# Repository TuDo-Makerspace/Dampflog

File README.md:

# Dampflog <!-- omit in toc -->

A synthesizer built from an [old Conrad Train whistle PCB](docs/DLP_Manual.pdf)

> This project was created during the [TU-DO Makerspace's Makerthon #1](https://www.instagram.com/p/CwGRmoHKHiY/?igshid=MzRlODBiNWFlZA==)!

# Table Of Contents <!-- omit in toc -->
- ["Dampflockpfeife" - The Steam Locomotive Whistle](#dampflockpfeife---the-steam-locomotive-whistle)
	- [Product Description](#product-description)
	- [The Circuit](#the-circuit)
		- [1. Power stage](#1-power-stage)
		- [2. Trigger/Gate circuit](#2-triggergate-circuit)
		- [3. Oscillator](#3-oscillator)
		- [4. Output Stage/Amplifier](#4-output-stageamplifier)
- [Background - The Makerthon](#background---the-makerthon)
- [Hacking the PCB](#hacking-the-pcb)
	- [Power Input](#power-input)
	- [Audio Output](#audio-output)
	- [Original Controls](#original-controls)
	- [HOLD Switch](#hold-switch)
	- [Gate Input](#gate-input)
	- [Pitch Control](#pitch-control)
		- [Initial Approach](#initial-approach)
		- [Time to get serious](#time-to-get-serious)
		- [Screw CV, we're going full MIDI](#screw-cv-were-going-full-midi)
		- [A PCB to rule them all](#a-pcb-to-rule-them-all)
- [The Result](#the-result)
- [Future plans](#future-plans)

## "Dampflockpfeife" - The Steam Locomotive Whistle

> Pardon the crude picture, I unfortunately didn't take any pictures of the PCB before I started hacking it.

### Product Description

The "Dampflockpfeife" is a [Printed Circuit Board that was published by Conrad Electronics in 1997 as a DIY soldering set for model train enthusiasts](docs/DLP_Manual.pdf). It attempts to mimic the sound of a steam locomotive whistle when activated. The circuit board is intended to be integrated into a model train track setup, where it can be activated in response to a passing train. To adjust the whistle sound, the PCB features two potentiometers — one for adjusting the pitch and another for setting the duration of the whistle blast. Activating the sound requires short-circuiting two contacts on the PCB, which can be achieved, for example, by employing a button or a sensor mechanism.

Here's a showcase of how the Whistle sounds:

https://github.com/TU-DO-Makerspace/Dampflog/assets/12089409/401a1205-c79d-425e-badc-b6d5c987373b

As you can hear, it does somewhat resemble a steam locomotive whistle, albeit rather poorly. That being said, a digital solution at the time would likely have been signficantly more expensive.

### The Circuit

Given its publication date, it should not come as a surprise that this circuit is devoid of any digital components. The whistle sound is synthesized entirely through analog means. Fortunately, the PCB's manual is, despite its age, [readily accessible online](docs/DLP_Manual.pdf). It offers a comprehensive resource, featuring a circuit description, a complete schematic, and even a PCB layout. While the manual is in German, fear not, as we will provide a comprehensive coverage of the circuit here.

Here's the schematic of the circuit:

The circuit can be split into four parts:

- 1. Power stage
- 2. Trigger/Gate circuit
- 3. Oscillator
- 4. Output Stage/Amplifier

#### 1. Power stage

On the first glance we can recognize a full bridge rectifier, indicating that the Circuit takes AC as an input. I initially found it somewhat peculiar but as I later found out, this choice was made to ensure compatibility with "Märklin" model train tracks, which, in contrast to their competitors, rely on AC voltage. According to various sources, this voltage typically falls within the range of 16 to 24 volts. While I'm no expert in model trains, I did have the fortunate opportunity to recently talk with someone knowledgeable in the field. They explained me that this unique reliance on AC voltage is a rather quirky characteristic of Märklin model trains.

Now, returning to the circuit itself: As mentioned, the AC voltage first passes through a full bridge rectifier (D1-D4) to convert it into a pulsating DC signal. Subsequently, this signal is smoothed out by a 100uF capacitor (C12). The stabilized voltage is then further regulated down to a consistent 12 volts via a 7812 linear regulator (IC1). This 12-volt output is then used as the supply voltage to power the remaining components of the circuit.

For my intents and purposes the whole power section was not needed. Instead, I simply used a 12V DC power supply and connected it directly to the 12V rail.

#### 2. Trigger/Gate circuit

As I delved into the schematic, one symbol immediately captured my attention: the NE555 timer IC. At first glance, I presumed it might be responsible for generating the whistle tone itself, but I quickly discovered that it operates in monostable/one-shot mode to generate a temporary gate signal. This gate signal serves to trigger the oscillator. Its duration is adjustable via potentiometer P2, allowing for a range spanning 1 to 10 seconds based on the potentiometer's setting.

To output a gate signal, a switch connected to the trigger input of the NE555 (labeled "Start" in the schematic) must be closed. This action pulls down the trigger pin and prompts the NE555 to produce a high signal at output pin 3, sustaining it for the preconfigured duration. This signal subsequently forward-biases transistor T3. Since the collector of T3 is connected to the base of T2, T2 becomes reverse-biased as a result. If no gate signal is present (default state), T2 is forward-biased via the pull-up resistor R4, which keeps the feedback path of the oscillator grounded, preventing it from generating any tone. With T2 in a reverse-biased state, the feedback path is no longer held down, enabling the oscillator to oscillate freely and synthesize the desired tone.

#### 3. Oscillator

The oscillator is arguably the most important part of the entire circuit. It somewhat resembles a relaxation oscillator built around an LM741 operational amplifier (OP-AMP), albeit with a distinct set of quirks that give it its unique character.

Firstly, the positive feedback loop takes an unusual turn as it's AC-coupled via capacitors C1 and C2. Further, what sets this oscillator apart and makes it particularly fascinating, is the inclusion of an NPN transistor, T1 within the feedback path. This transistor operates in a rather atypical diode configuration, with its emitter connected to the more positive rail. Its role? To introduce a subtle touch of chaos by injecting noise into the feedback path. But wait, there's more. The op-amp's output is also coupled to the "Offset Null" pin via capacitor C7, further contributing to the circuit's distinctive noisy sound. The noise injected into the feedback path causes subtle changes in the oscillator's frequency. This is precisely what gives this PCB its steam locomotive" sound. The rest of the circuit aligns more closely with a standard OP-AMP relaxation oscillator.

The frequency of this oscillator is adjustable through potentiometer P1, which defines the voltage propagated through the positive feedback pathway. On the inverting input of the OP-AMP, an RC circuit formed by R8 and C6 generates a triangular waveform. When P1's resistance decreases, the voltage in the positive feedback path decreases as well. Consequently, the triangular wave at the non-inverting input catches up to the inverting input faster, escalating the oscillator's frequency. When P1 reaches a low-enough resistance, the propagated voltage drops sufficiently low to stabilize the oscillation. In this state, only the eerie and somewhat spooky sound produced by the noise feedback path remains audible. You can listen to a recording of this peculiar sound [here](https://soundcloud.com/user-631734174/bc548-diode-configuration-noise).

An interesting side effect of this stabilization is that the oscillator experiences hysteriesys due to it's schmitt-trigger like positive feedback. As a result, P1 must be turned further back to retrigger the oscillation.

In total, the oscillator offers a frequency spectrum spanning approximately 116Hz (at infinite resistance) to 700Hz (at the point of stabilization). This equates to roughly 2.5 octaves of range, covering pitches from A#2 to F5.

Below are a couple of screenshots of LTSpice simulations to further illustrate the behaviour of the oscillator.

LT SPICE STUFF HERE

A crucial aspect of this circuit: The relationship between frequency and the potentiometer P1 follows an inversely multiplicative response. At lower resistances (corresponding to higher frequencies), even slight adjustments to P1 produce rapid frequency shifts. In contrast, at higher resistances (corresponding to lower frequencies), making similar changes to P1 yields only slight changes in frequency. Ideally, for precise pitch control, we would expect this behavior to be exponential, not inverse multiplicative. This characteristic became a significant challenge when attempting to implement 1V/Octave pitch control, as we will explore later.

Additionally, the LM741 exhibits an intersting trait: At higher frequencies, it exhibits a low-pass filtering effect. Lower frequencies result in a more square-like output, while higher frequencies manifest as a more triangular waveform. This phenomenon can likely be attributed to the slew rate of the LM741, and it controbutes to a distinctive and appealing character to the resulting sound.

#### 4. Output Stage/Amplifier

To be honest, I don't possess enough experience in the field of transistor amplifiers, and given that the output stage is not really relevant for my project, I haven't delved deeply into its functionality. I have a vague suspicion that T4 and T5 might play a role in amplifying the signal voltage, while the complementary push-pull amplifier comprising T7 and T6 might be responsible for current buffering. However, as mentioned, I'm not entirely certain so I welcome any corrections or clarifications if I'm off the mark.

## Background - The Makerthon

Before discussing the modifications I made to the circuit board, I'd like to provide some context for this project. This project was born out of a Hackathon organized at our Makerspace, called "Makerthon". The theme, albeit not mandatory, was to "Upcycle" old electronics that we had lying around in the Makerspace. The time frame for the Hackathon was about two and a half days.

During the first day the task was to scavange for old electronics and brainstorm ideas for potential projects. After digging through an old box of PCBs I stumbled upon the Dampflog PCB. From there, it didn't take long to find the manual online and jump to the idea of turning this thing into a musical synthesizer!

## Hacking the PCB

After thoroughly examining the circuit, it was time to transform the PCB into a musical synthesizer. Before I could wield my trusty soldering iron, I needed to formulate a roadmap of the features I wanted to "hack" into the PCB. Here's my initial list of requirements:

- 12V DC Power Input
- 3.5mm Jack audio output with volume control
- A HOLD switch to permanently enable the gate signal
- A 0-5V Gate input to trigger the gate signal
- A 1V/Octave CV input to control the pitch

Beyond these additions, I wanted to ensure that the device retained its original functionality. To achieve this, I included a push-button for manual gate signal triggering, along with potentiometers to adjust the gate signal duration and pitch manually.

For housing the PCB, I repurposed an old metal box that had once contained a [data transfer switch (KVM Switch)](https://www.amazon.com/Kentek-Parallel-Peripherals-Devices-Printer/dp/B07KWRWLRN)—which we happened to have lying around in the makerspace. Typically, I would have opted for a 3D-printed enclosure, but as mentioned prior, this project was created during a Hackathon, and I simply didn't have the luxury of time for enclosure design and printing. As a playful touch, I even gave the enclosure a neat little spray-paint job, just for the fun of it.

### Power Input

Adding a 12V DC power input was rather trivial. I simply connected a 2.1mm DC barrel jack to the 12V rail of the PCB with a switch in between to turn the device on and off. I also added a small red power LED next to the Jack to indicate that the device is powered on.

I tried to solder the power wires as close to the power stage as possible to maximize the utilization of the power capacitors on the PCB. The DC jack found its home on the front side of the enclosure, while the switch was thoughtfully situated on the back side.

In hindsight, I realize that it might have been more ergonomically advantageous to swap the positions of the jack and the switch.

PICTURE OF JACK HERE

### Audio Output

Adding audio output was also pretty straight forward. I simply connected a 3.5mm audio jack to the output of the amplifier. To provide volume control for the output signal, I introduced a potentiometer which serves as a voltage divider.

The potentiometer and jack were mounted on the front side of the enclosure for easy accessibility.

PICTURE OF AUDIO JACK HERE

It's important to know that the output can reach up to 10VPP, which is **NOT** suitable for headphones. I recommend only
using the device in combination with an audio interface or external amplifier. The volume should always be turned down first
before connecting the device to an audio interface or amplifier.

The advantage of such high peak-to-peak voltage is that it can be used to drive a speaker directly and can also interface easily with eurorack modules which also operate at similar voltage levels.

### Original Controls

As previously mentioned, it was essential to retain the device's original intended functionality. One addition was a green arcade-style push button mounted on the top side of the enclosure to serve as a trigger for the gate signal. I also mounted two potentiometers on the top side to control the duration of the gate signal and the pitch. It should be noted that I used a 200k pot instead the original inteded value of 50k. This modification expanded the available pitch range. A 50k pot couldn't quite reach the lower frequency limits of the oscillator.

PICTURE OF ORIGINAL CONTROLS HERE

### HOLD Switch

Incorporating a HOLD switch proved to be the first slightly more complicated addition to the circuit. After some consideration, I determined that a switch connected in parallel to transistor T3 would provide the most effective solution. When this switch is in the closed position, it essentially replicates the scenario where T3 is forward-biased. Consequently, this keeps T2 in a reverse-biased state, ensuring that the oscillator remains continually enabled.

For user convenience, the HOLD switch has been mounted next to the trigger button.

PICTURE OF HOLD SWITCH HERE

### Gate Input

To introduce a GATE support, I drew inspiration from the design of the HOLD switch. I incorporated a 3.5mm jack, connected to an NMOS transistor positioned in parallel with T3. To guarantee that the MOSFET remains consistently off when the jack is not used, I added a 220k Pull-Down resistor at the gate.

Additionally, for added protection against accidental voltage spikes (e.g., during jack cable insertion), I integrated a 10k resistor between the jack tip and the MOSFET's gate. This arrangement effectively increases the RC constant (C being the MOSFETS capacitance), safeguarding the MOSFET from potential damage.

PICTURE OF GATE JACK HERE

Without revealing too much ahead, I made some slight modifications to the GATE input during the course of the project. More on that later.

To put the GATE support to the test, I connected my trusyworthy Arturia Keystep to the GATE input, only to discover that the oscillator isn't particularly well-suited for GATE input, at least not in the traditional sense. You see, the oscillator exhibits a slight attack duration and a rather brief decay time. This means it requires a significant amount of time to reach its intended pitch but quickly ceases once the GATE signal drops. Consequently, rapid GATE signals fail to give the oscillator adequate time to achieve its intended pitch, resulting in a "chopped" tone. This behavior is primarily attributed to the fact that the oscillator relies on RC circuits, which are intentionally designed to take time to charge up.

Despite this, I still found the GATE input to be genuinely useful in only two scenarios:

- When the BPM/tempo setting allows the oscillator sufficient time to attain its desired pitch.
- When creating a percussive, choppy sound effect.

Interestingly, I found the second scenario to be a seriously cool unintended feature. It particularly shines when the oscillator is pushed to its upper limits, allowing only the noise within the feedback path to be gated. This makes for a dirty, industrial screechy sound which is great for harsher techno tracks. You can explore a sample of this distinctive sound, enhanced with a touch of distortion, reverb, flanging, and some percussion, by [clicking here](https://soundcloud.com/user-631734174/dampflog-gate-noise-test).

### Pitch Control

#### Initial Approach

To at least deliver a proof of concept for the end of the Makerthon I had to at least implement some form of half-arsed pitch control. For the sake of demonstration I
disattached the Pitch potentiometer P1 and soldered in a generic Jellybean transistor in place. Then I added a 3.5mm jack for a CV input and simply soldered it with a
voltage divider and rather large base resistor to the transistors base until I got a somewhat usable range of pitch. Obiously the scale was completely out of tune and far from linear, but It was enough to demonstrate that the thing can be used to produce melodies.

https://github.com/TU-DO-Makerspace/Dampflog/assets/12089409/d06b69a9-8a2e-4bfc-8f98-e92429bd2175

#### Time to get serious

Implementing pitch control became a weeks-long journey. By the end I had suffered from serious circuit design brain-rot. Prior to working on this project, my experience with analog operation of transistors was somewhat limited. This was further complicated by attempting to implement 1V/Oct pitch control on a circuit that was never originally designed for such a purpose. I also wanted to avoid altering the original circuit as much as possible.

After some initial, albeit clueless experimentation with transistors, it became very clear that I couldn't sidestep a deeper understanding of these components if I wanted to achieve precise 1V/Oct control. Fast forward a few weeks, and I had consumed over 40 hours of electronic circuits lectures delivered by Prof. Behzad Razavi from the University of California in Los Angeles, which are freely available online. I can't emphasize enough how invaluable these lectures were, providing a significantly more comprehensive and insightful overview of transistors compared to my university's electronic circuit course. After absorbing a substantial amount of knowledge from these lectures, I felt ready to take a more educated approach to solve the pitch control conundrum.

First, I examined how some Voltage-Controlled Oscillators (VCOs) implement 1V/Oct pitch control. Typically, this involves exponentializing a linear signal using a transistor. This exponentialization is necessary because human perception of pitch is inherently exponential. In the equal-tempered scale, for instance, the frequency of notes increases exponentially by the twelfth root of 2. Of course, the implementation goes beyond simply connecting a transistor's base to the 1V/Oct input; it typically includes circuitry for gain calibration, scaling, and base note adjustment. However, these details need not haunt us, as this approach cannot be directly applied to our oscillator anyaways.

Here's the crux of the issue: our oscillator exhibits inverse-multiplicative growth, something akin to the form a * 1/x + b. 

This response is neither linear nor exponential. If it were linear, we could simply use a transistor to exponentialize it and achieve 1V/Oct pitch control. If it were already exponential, we could use a transistor with heavily supressed gain, thus operating it nearly lineary (akin to a voltage-controlled resistor). Unfortunately, the oscillator's response falls into an awkward zone where it somewhat behaves like an exponential function but not quite. Yes, Low frequencies experience a slow rate of change, and high frequencies experience a rapid rate of change, but it's still not quite exponential. To test the extent of this inaccuracy, I decided to construct a test circuit with a transistor that roughly operated as a voltage-controlled resistor. To achieve this, I selected an extraordinarily large base resistor (around 5M in this case) to suppress the transistor's gain to the point where its beta value and base resistor dominated the gain.

The next step involved sweeping the transistor's base voltage using a function generator and measuring the oscillator's frequency. The outcome was predictably disappointing. As anticipated, the response exhibited inverse-multiplicative behavior, with the oscillator stabilizing at high frequencies. I unfortunately only measured the frequency response within the operating range of the
transistor, so to better illustrate the inverse-multiplicative behavior the graph below shows the frequency to base voltage response on a equivalent LTSpice simulated circuit:

It should be noted that the real oscillator does not reach frequencies below 116Hz, other than that the response is similar enough to demonstrate my point.

Notice the grey lines in the graph. These represent note intercepts. Taking a quick glance at the note intercepts, it becomes apparent that the response only approximates exponential pitch within an exceedingly narrow range. Ideally we'd want them to be equally spaced on the x axis to implement 1V/Oct. If we plot the distances between each note intercept, this discrepancy becomes even more pronounced. Here's actual data from the real oscillator:

As we can see pitch only behaves linearly proportional around 3.5V with a steps size of about 60mV/Note. For the setup in question, 3.5V corresponded to approximately 300Hz, which falls within the 4th octave. As we leave 3.5V this proportion begins to drift away from the close to constant 60mV, which will cause the pitch to become out of tune.

I actually went so far as to construct a 1V/Oct scaling circuit to connect my Keystep keyboard. While I achieved reasonably linear behavior in the fourth octave (as corresponding to the "sweet spot" where the inverse-multiplicative function is most similar to the exponential pitch function), venturing beyond the octave unsuprisingly resulted in severely out-of-tune frequencies. This deviation escalated significantly the further we moved away from this "sweet spot."

#### Screw CV, we're going full MIDI

At this point, it dawned on me that trying to tackle the inverse-multiplicative quirk with analog wizardry just wasn't worth the headache. I should probably mention that I'm currently pursuing a degree in computer engineering. Now, you know how it is – us computer engineers often enjoy poking fun at electrical engineers by solving problems with lines of code instead of soldering irons. Jokes aside, it really seemed like the easiest and most practical solution here was to go digital, and more specifically, to embrace the wonders of microcontrollers and DACs. And if we're making the switch to digital, why not go all the way and swap out CV with MIDI?

The idea is pretty straightforward: the MCU receives MIDI signals via a MIDI port, then converts them into DAC values using a handy lookup table. These DAC values, in turn, dictate the behavior of a transistor nestled within the oscillator's feedback path. Now, we no longer need to fuss about the intricacies of whether the oscillator operates linearly or exponentially. All we have to do is tell the MCU which note corresponds to which DAC value, and presto – we've got the right frequency.

With a DAC, it's still important to maintain control over the transistor's gain suppression while ensuring that the gain remains substantial enough to cover the oscillator's full frequency range with the MCU's and DAC's supply voltage. For the DAC, I opted for an MCP4921, which has 12 bits of resolution and the convenience of an external reference voltage. This choice proved more than adequate for accurately mapping MIDI data to the oscillator's frequency range, and that despite loosing a portion of the DAC range due to the absence of biasing its output to the operating range of the transistor.

#### A PCB to rule them all

In order to create a digital interface for controlling the Dampflog, it became evident that a PCB would be practical for the task. Consequently, I proceeded to designing a PCB that incorporates various key elements, including MIDI circuitry, an STM8S development board as MCU, a DAC, and a couple of additional features like a GATE output and portamento functionality. The GATE output allows for MIDI-based GATE control. Additionally, I integrated switches to transition between manual oscillator operation and digital control. For the GATE function, I simply applied an OR logic operation to the MCU's GPIO output and the previously implemented analog GATE inputs. This spared me from having to add another switch, which would convolute the device even more.

It's worth noting that I designed the PCB to fit within a single layer, allowing for in-house etching. The red traces represent jumper wires. In retrospect I was rather naive about the clearances, which lead to some challenges during the etching process (some traces were close they ended up shorting). Despite these hiccups, the PCB eventually performed its intended function.

Now, I won't delve into further details of the interface board in here, as it deserves a dedicated README of its own. You can find comprehensive coverage of the interface board, including insights into the MCU's firmware, in the README file within the InterfaceBoard directory.

## The Result

Here's the final block diagram of the circuit, including the interface board:

So, what I've got here is a steam locomotive whistle synth that's grooving to the MIDI rhythms. It's kinda hilarious to think that someone originally snagged this thing for their model train setup, and now, more than two decades later, it's belting out some seriously gritty techno tunes.

Let's be real, this thing has no business being so absurdly over-engineered, especially when you consider its somewhat limited frequency range and the fact that it probably won't exactly blow your mind with its sound. But that doesn't matter because this project was an absolute blast! I learned more about transistors in a few months than I did in my entire four years of studying! Plus, I dove headfirst into the world of pitch scaling, data analysis, signal wizardry, and the art of wrangling DACs. Now that's something!

## Future plans

Right now, I'm just happy to call this project a wrap. Don't get me wrong, it's been lot's of fun, but honestly, at this point I just want to crank it up and start making some music. That said, I've got some ideas brewing in the back of my mind. I'm thinking about cooking up a standalone synth or maybe even diving into the world of eurorack modules with this thing. I'd essentially take a stripped-down version of the train whistle PCB and give it multiple voices by using multiple oscillators instead of just one. It should be a pretty straightforward endeavor since most of the ICs I'd need for this task come in dual and/or quad packages.

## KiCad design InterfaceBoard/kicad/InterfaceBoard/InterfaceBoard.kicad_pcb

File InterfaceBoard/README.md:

# Dampflog Interface Board

> This README is WIP

Within this directory, you will find the firmware and KiCad project for the Dampflog Interface Board. The primary objective of this interface board is to equpt the Dampflog with a digital interface, specifically through MIDI. It accepts MIDI input and manages the Dampflog's gate and pitch in accordance with the note command it receives. It also has a MIDI thu output, allowing the dampflog to be daisy-chained with other MIDI devices.

# Hardware

## Showcase

The Interface Board resides as a single layer PCB withing the enclosure of the Dampflog. It is connected to the [Dampflockpfeife PCB](../README.md) and other external components through JST XH connectors. The board accepts a 12V power supply which is regulated down
via a linear regulator to 3.3V through a STM8S devboard that resides on the Interface Board. While this voltage difference is not ideal, the current consumption is low enough that the regulator does not become hot.

Here's the schematic:

And here's the PCB layout:

The red traces do not represent real traces, but rather jumper wires. In hinsight I was overly optimistic with the clearances on the PCB. As a result there were some traces that ended up shorting after the board was etched. Some of them could be saved by seperating the traces with a knife, but others were so messed up I simply broke the connections and used jumper wires instead. 

## Overview

The Interface Board consists four parts:

- MIDI Input & Thru
- Gate Output
- Pitch Control
- Microcontroller

### MIDI Input & Thru

For the MIDI Input and Thru circuit, I simply referenced a [template design I made a while ago](https://github.com/TU-DO-Makerspace/KiCAD-MIDI-Templates). The MIDI IN circuit operates on 3.3V and uses a 6N137 Optocoupler. The MIDI THRU circuit is connected in parallel to the optocoupler output and simply buffers the incomign signal to the MIDI thru port.

## Gate Output

For the GATE output, the board actually accepts the manual GATE controlls (Gate JACK and HOLD switch) as an input, and simply OR's it with the Microcontroller's GATE output using two diodes and a pull down resistor. The MCU's GATE output is simply driven by a GPIO.

## Pitch Control

The pitch control circuit primarily comprises three key components: a DAC, a buffer, and a common-emitter transistor connected to the Dampflockpfeife PCB's oscillator, thereby controlling the pitch. Situated between the DAC and the buffer is an adjustable low-pass filter which allows for slide/portamento by delaying changes in the CV signal.

The chosen DAC is a [MCP4921](https://ww1.microchip.com/downloads/en/DeviceDoc/21897B.pdf), providing 12-bit resolution and can be controlled via an SPI interface. The buffer is implemented using a single-supply rail-to-rail [MCP6002](https://www.reichelt.de/index.html?ACTION=7&LA=3&OPEN=0&INDEX=0&FILENAME=A200%2FMCP6002_MCP6004_MIC.pdf).

The buffer's output is wired to a 2N2222A NPN transistor's base with a 2.2MOhm resistor.
This controls the pitch of the oscillator. The high base resistor supresses the transistor's gain, providing a more linear current control. With that said: A too large base resistor would limit the circuits ability to step through the oscillator's complete pitch range. Hence, the base resistor was chosen to still allow the DAC to reach the full pitch range of the oscillator with the MCU's 3.3V supply voltage. Another issue with large resistances is that the paths high impedance becomes more susceptible to noise. To minimize this effect, the trace was kept as short as possible. The ground plane surrounding the trace also helps to supress noise.

Lastly, the DAC also accepts a external reference voltage, defining its maximum output voltage. A smaller reference voltage gives us smaller voltage steps, and thus finer resolution at the expense of range. To maximize resolution, we want the external reference voltage reference to match the base voltage required to reach reach the highest possible tone of the oscillator. To achieve this, the DAC's external voltage reference is connected to a trim potentiometer that can be adjusted to maximize the DAC's resolution.

PICTURE OF TRIM POT

The choice of components was mostly based on what was readily available in our Makerspace already.

## Microcontroller

The microcontroller forms the brain of the interface board. It is responsible for reading the MIDI input and consequently controlling the Damplogs GATE and pitch. The chosen MCU is a STM8S103F3P6 which is not directly mounted on the interface board, but rather comes on a devboard. The devboard also provides a 3.3V regulator which also provides a voltage supply for other ICs on the interface board.  

The STM8S can be programmed with an ST-LINK using the SWIM interface. The cheap chinese ST-LINK clones will also do the job. For those wondering why I didn't choose a more common platform such as an Arduino or a Pi Pico. Well, for one, the STM8 devboards are dirt cheap (we're talking 80Cents per board). Another reason is because I have past experience with MIDI on the STM8S platform, allowing me to recycle a good chunk of code. The firmware will be discussed in the next section.

# Firmware

The firmware is written in C and compiled with SDCC. I also make use of the [STM8S Standard Peripheral Library](https://github.com/bschwand/STM8-SPL-SDCC) which provides a minimal abstraction layer for the STM8S's peripherals. The firmware is rather simple, and simply listens for UART RX interrupts. When a UART RX interrupt has been received, it is evaluated for MIDI. If the input forms a valid and supported MIDI message, the appropriate action is taken. Currently, the firmware supports the following MIDI messages:

- `Note On`
- `Note Off`

Upon `Note On`, the note number is mapped to a DAC value using a lookup table found in [firmware/include/midi_2_dac.h](firmware/include/midi_2_dac.h). The DAC value is then written to the DAC via SPI and the GATE is turned on. Upon `Note Off`, the GATE is simply turned off.

Notes that are out of the oscillators range are simply mapped to the highest or lowest possible note.

Perhaps as an interesting side note: When a debug build is compiled, the firmware will also listen for SYSEX messages. There are two supported SYSEX messages:

- `SET DAC <DAC VALUE MSB> <DAC VALUE LSB>`
- `SET GATE <GATE VALUE>`

The `SET DAC` command allows one to manually set the DACs value. This is actually used to generate the "MIDI 2 DAC" lookup table found in [firmware/include/midi_2_dac.h](firmware/include/midi_2_dac.h) via a python script found in [firmware/tools/tune.py](firmware/tools/tune.py). The `SET GATE` command allows one to manually set the GATE output, which proved to simply be useful for debugging and testing during development.

The debug build also prints a verbose log via UART. To save space and especially processing time, logging and SYSEX are disabled in non-debug builds.

For a more elaborate understanding of the firmware, feel free to browse its source code. The codebase is pretty small and I have made sure to provide a fair amount of comments.

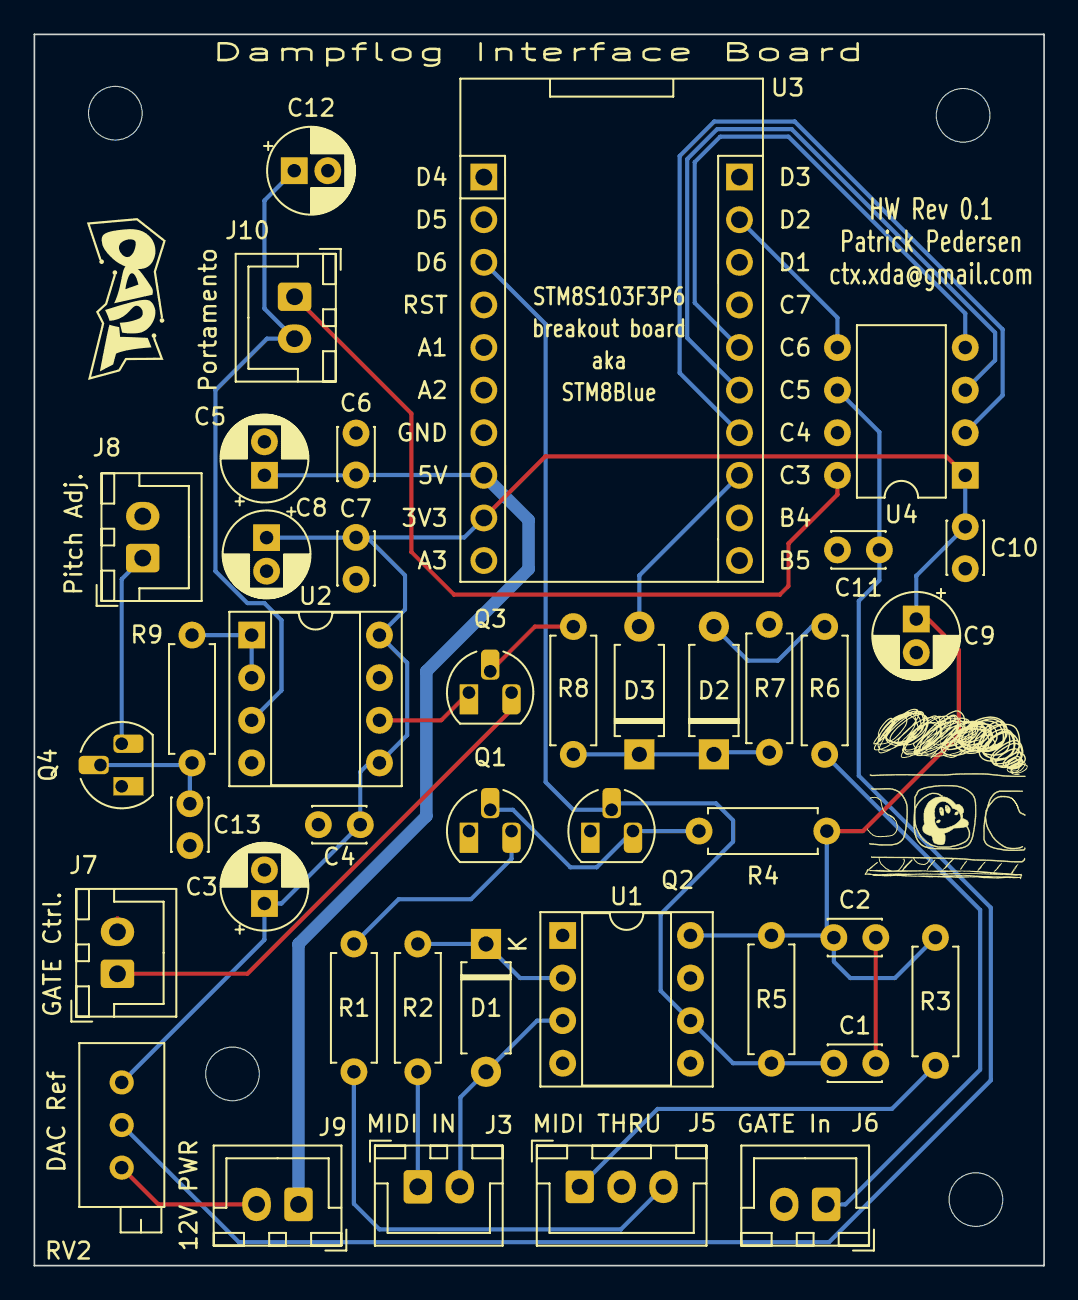
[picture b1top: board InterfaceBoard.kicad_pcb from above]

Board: 2 copper layers, 60.2 x 73.4 mm, 41 parts (0 on the bottom side), 27 nets.

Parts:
C1: 15pF; C_Disc_D3.0mm_W2.0mm_P2.50mm
C2, C4, C6, C7, C10, C11: 100n; C_Disc_D3.0mm_W2.0mm_P2.50mm
C3, C9: 1u; CP_Radial_D5.0mm_P2.00mm
C5, C8: 10u; CP_Radial_D5.0mm_P2.00mm
C12: ???; CP_Radial_D5.0mm_P2.00mm
C13: 47n; C_Disc_D3.0mm_W2.0mm_P2.50mm
D1, D2, D3: 1N4148; D_A-405_P7.62mm_Horizontal
J3: JST MIDI IN; JST_XH_B2B-XH-A_1x02_P2.50mm_Vertical
J5: JST MIDI THRU; JST_XH_B3B-XH-A_1x03_P2.50mm_Vertical
J6: JST GATE IN; JST_XH_B2B-XH-A_1x02_P2.50mm_Vertical
J7: JST GATE CTRL; JST_XH_B2B-XH-A_1x02_P2.50mm_Vertical
J8: JST Pitch Adj.; JST_XH_B2B-XH-A_1x02_P2.50mm_Vertical
J9: JST PWR; JST_XH_B2B-XH-A_1x02_P2.50mm_Vertical
J10: JST Portamento Pot; JST_XH_B2B-XH-A_1x02_P2.50mm_Vertical
Q1, Q2, Q3: 2N7000; TO-92_HandSolder
Q4: PN2222A; TO-92_HandSolder
R1: 10; R_Axial_DIN0207_L6.3mm_D2.5mm_P7.62mm_Horizontal
R2: 220; R_Axial_DIN0207_L6.3mm_D2.5mm_P7.62mm_Horizontal
R3: 33; R_Axial_DIN0207_L6.3mm_D2.5mm_P7.62mm_Horizontal
R4, R5, R6, R8: 10k; R_Axial_DIN0207_L6.3mm_D2.5mm_P7.62mm_Horizontal
R7: 220k; R_Axial_DIN0207_L6.3mm_D2.5mm_P7.62mm_Horizontal
R9: 3M; R_Axial_DIN0207_L6.3mm_D2.5mm_P7.62mm_Horizontal
RV2: 100k; Potentiometer_Bourns_3296X_Horizontal
U1: 6N137; DIP-8_W7.62mm_Socket
U2: MCP6002-xP; DIP-8_W7.62mm_Socket
U3: STM8S103F3P6_Blue
U4: MCP4921; DIP-8_W7.62mm

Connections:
+12V: C5.1, C6.1, J9.1, U3.8 (5V/VUSB)
/CV: C13.1, Q4.2 (B), R9.2
/DAC OUT: J10.1, U4.8 (Vout)
DAC CS: U3.14 (PC4(HS)/TIM1_CH4/CLK_CCO/AIN2/[TIM1_CH2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), U4.2 (~CS)
DAC LDAC: U3.19 (PD2(HS)/AIN3/[TIM2_CH3]), U4.5 (~LDAC)
DAC SCK: U3.15 (PC5(HS)/SPI_SCK[TIM2_CH1]), U4.3 (SCK)
DAC SDI: U3.16 (PC6(HS)/SPI_MOSI[TIM1_CH1]), U4.4 (SDI)
GATE: J7.1, Q3.3 (D)
GATE GPIO: D3.2 (A), U3.13 (PC3(HS)/TIM1_CH3[TLI][TIM1_CH1N])
GATE JACK: J6.1, R6.1
GND: C1.2, C2.2, C3.2, C4.2, C5.2, C6.2, C7.2, C8.2, C9.2, C10.2, C11.2, C12.2, C13.2, J5.2, J6.2, J7.2, J8.2, J9.2, Q1.1 (S), Q2.1 (S), Q3.1 (S), Q4.1 (E), R7.2, RV2.3, U1.5 (GND), U2.4 (V-), U2.6 (-), U3.7 (GND/VSS), U4.7 (Vss)
MCU VCC: C2.1, C3.1, C4.1, C7.1, C8.1, C9.1, C10.1, R3.1, R4.2, R5.2, RV2.1, U1.8 (VCC), U2.5 (+), U2.8 (V+), U3.9 (3V3/VDD), U4.1 (Vdd)
MIDI IN DATA: C1.1, Q2.2 (G), R5.1, U1.6 (VO), U3.3 (UART1_RX/AIN6/(HS)PD6)
unnamed: D1.2 (A), J3.2, U1.3 (C)
unnamed: D1.1 (K), R2.2, U1.2 (A)
unnamed: D2.2 (A), R6.2
unnamed: D2.1 (K), D3.1 (K), R7.1, R8.1
unnamed: J3.1, R2.1
unnamed: J5.1, R3.2
unnamed: J5.3, R1.1
unnamed: C12.1, J10.2, U2.3 (+)
unnamed: Q1.3 (D), R1.2
unnamed: Q1.2 (G), Q2.3 (D), R4.1
unnamed: Q3.2 (G), R8.2
unnamed: R9.1, U2.1, U2.2 (-)
unnamed: C11.1, RV2.2, U4.6 (Vref)
PITCH: J8.1, Q4.3 (C)

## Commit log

2023-09-14 InterfaceBoard: Firmware: Successful DAC test
2023-09-18 Interface Board: Kicad: Minor fixes regarding JST connector orientation
2023-09-18 Interfaceboard: Firmware: Added SYSEX support for device configuration and calibration
2023-09-18 Interface board: Added WIP calibration script to generate C lut
2023-09-18 Interface Board: Calibration: Fill higher unspecified notes with max DAC value + Export CSV + Minor formatting changes
2023-09-18 Interface board: Midirx: Check status filter AFTER checking for SYSEX
2023-09-19 Interface Board: Added DEBUG build with logs + Changes to tools
2023-09-20 Interface board: MIDI: Implemented status filter for faster MIDI performance
2023-09-20 Interfaceboard: Makefile: Added DEBUG option which builts debug logs and SYSEX handling
2023-09-20 Interfaceboard: Added lots of comments
2023-09-21 Added README draft
2023-09-21 README: ChatGPT my beloved
2023-09-21 README: Added TOC
2023-09-22 README: Improvements
2023-09-22 README: Added Whistle demo vid
2023-09-22 README: Fixed showcase video
2023-09-22 README: Added schematic pics
2023-09-22 README: Added crude picture of Dampflockpfeife PCB
2023-09-22 README: Added pics documenting PCB hacks
2023-09-22 README: Minor fixes
2023-09-22 README: Added initial pitch demo
2023-09-22 README: Added hackathon context
2023-09-22 README: Decreased size of makerthon poster
2023-09-22 README: Added Interface board pics
2023-09-23 README: Added measurements for CV stuff
2023-09-23 README: Aligned CV images to center
2023-09-24 README: Centered more pics
2023-09-24 README: Added block diagram
2023-09-24 README: Omitted small signal analysis for now
2023-09-25 Interface board: Initial README commit
2023-09-25 Interface Board: README: Added more pics
2023-09-25 Interface Board: README: Added WIP disclaimer + Fixed MCP6002 reference
2023-09-25 Interface Board: README: Centered pics
2023-09-25 Interface Board: README: Fixed some links
2023-09-25 Interface Board: README: Reduced size of PCB image
2023-09-25 README: Corrected logic operation of GATE
2023-09-25 Interface Board: Firmware: Corrected comment
2023-10-03 Interface Board: Conform to sysex requirements of data bytes being <= 127 + Formatting
2023-10-03 Interface Board: Tools: Added automatic tuning script
2023-10-03 Minor updates
2023-10-03 Interface Board: Autotuner: Deal with cases where first note already exceeded for DAC val = 0
2023-10-03 Interface Board: Autotune: Use fixed header guards
2023-10-05 Removed garbage file
2023-10-05 Interface Board: Added EEPROM/Data flash MIDI2DAC LUT support
2023-10-06 Interface Board: MIDI 2 DAC: Initialize midi2dac lut at boot
2023-10-06 Interface Board: Autotune: Added EEPROM writing support + Stability fixes
2024-06-22 README: Added images
2024-06-22 Interfaceboard: Use stm8dce
2025-03-22 Minor correction
